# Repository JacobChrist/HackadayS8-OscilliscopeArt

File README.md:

# Oscilloscope Art at Hackaday Supercon8 (2024)

This project is documented here:

https://hackaday.io/project/198922-oscilloscope-art-at-hackaday-supercon-8

This repo contains supporting schematics, code and spreadsheets (or at least that's the plan)

## Some notes from markusthegeek​:

Be sure to use the Earle Philhower library for the Pi Pico with the Arduino IDE.  You must press the boot button when powering the board to program it the first time when using the Arduino IDE.

When you clone the repo use the "sip-header-code" branch if you want to use it with the S8 Hackaday Badge

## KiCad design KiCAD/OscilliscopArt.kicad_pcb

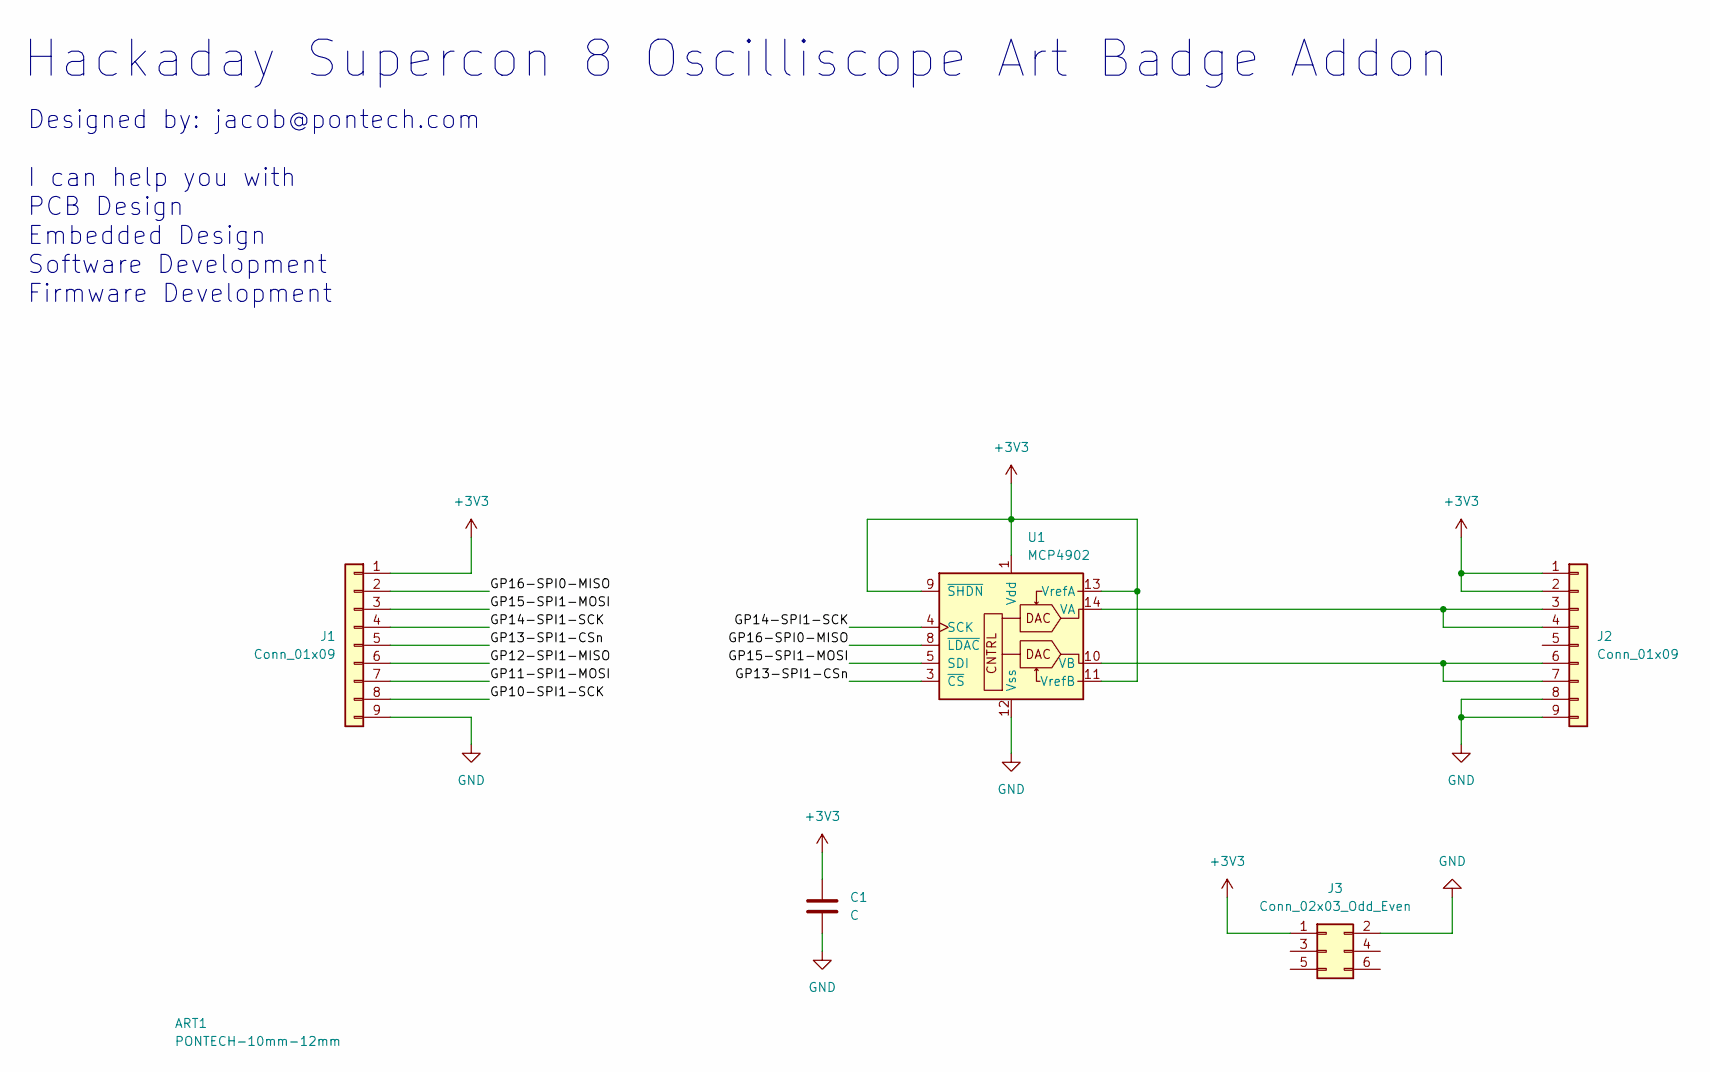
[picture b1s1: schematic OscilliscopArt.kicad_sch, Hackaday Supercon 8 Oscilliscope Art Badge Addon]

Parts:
ART1: PONTECH-10mm-12mm
C1: C; C_Disc_D5.0mm_W2.5mm_P2.50mm
J1, J2: Conn_01x09; SIP-9_22.3x3mm_P2.54mm
J3: Conn_02x03_Odd_Even; PinHeader_2x03_P2.54mm_Vertical
U1: MCP4902; DIP-14_W7.62mm_LongPads

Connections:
+3V3: C1.1, J1.1, J2.1, J2.2, J3.1, U1.1 (Vdd), U1.9 (~SHDN), U1.11 (VrefB), U1.13 (VrefA)
/GP10-SPI1-SCK: J1.8
/GP11-SPI1-MOSI: J1.7
/GP12-SPI1-MISO: J1.6
/GP13-SPI1-CSn: J1.5, U1.3 (~CS)
/GP14-SPI1-SCK: J1.4, U1.4 (SCK)
/GP15-SPI1-MOSI: J1.3, U1.5 (SDI)
/GP16-SPI0-MISO: J1.2, U1.8 (~LDAC)
GND: C1.2, J1.9, J2.8, J2.9, J3.2, U1.12 (Vss)
unnamed: J2.3, J2.4, U1.14 (VA)
unnamed: J2.6, J2.7, U1.10 (VB)

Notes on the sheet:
Hackaday Supercon 8 Oscilliscope Art Badge Addon
Designed by: jacob@pontech.com I can help you with PCB Design Embedded Design Software Development Firmware Development

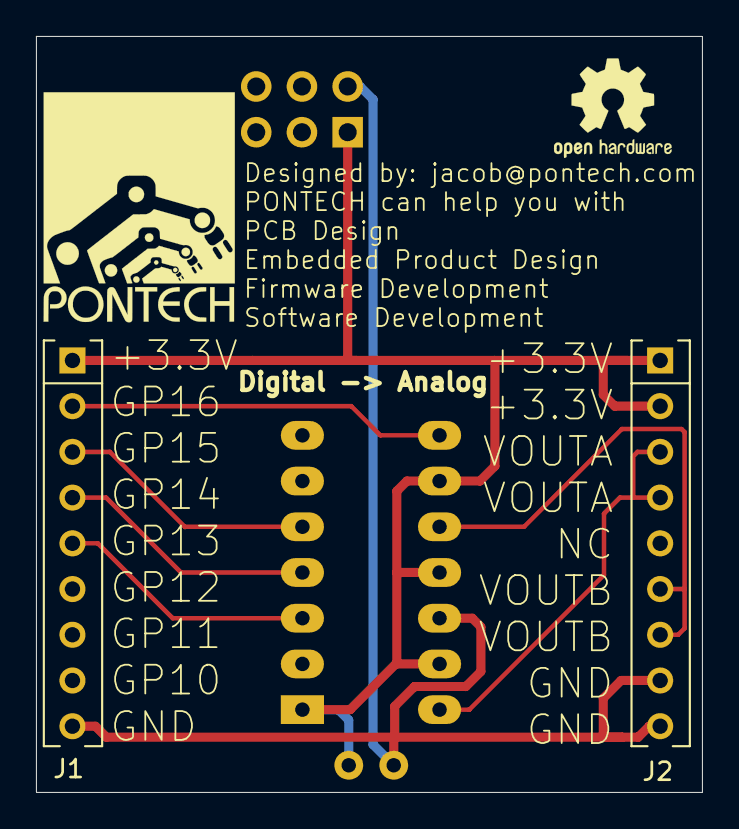
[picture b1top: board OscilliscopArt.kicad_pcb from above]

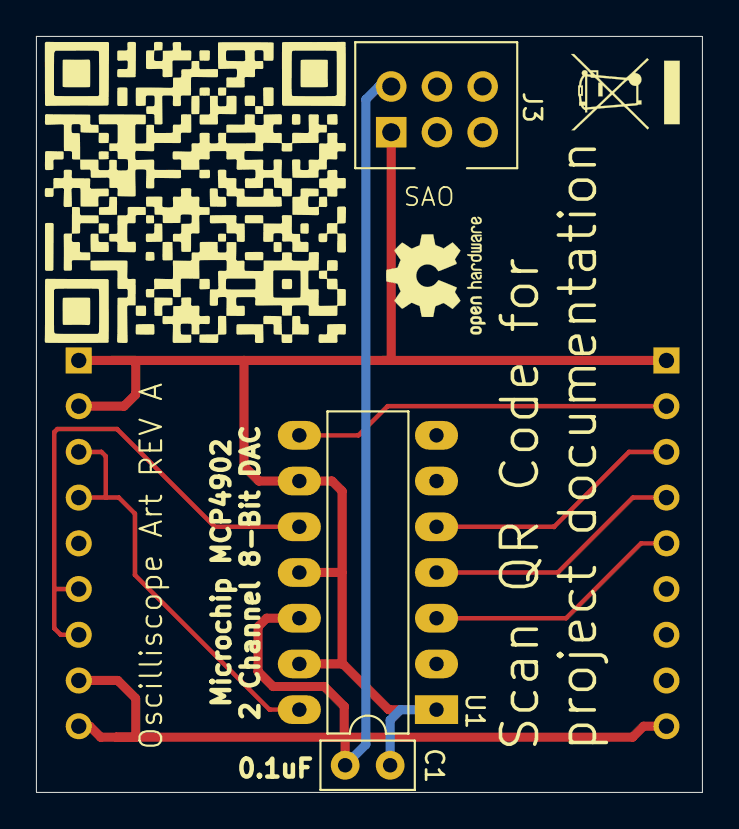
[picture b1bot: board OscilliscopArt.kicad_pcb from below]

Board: 2 copper layers, 37.0 x 42.0 mm, 6 parts (3 on the bottom side), 8 nets.

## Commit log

2024-10-20 Inital commit
2024-10-20 Added source code for the demo being shown at Supercon8
2024-10-21 Added SAO header
2024-10-21 REV-A Gerbers + Added WEE and Open Hardware Logos
2024-10-21 Added Excel Spreadsheet for generating art as code.
2024-11-01 Updated SPI port and chip select pins for running the boards off the SIP header on the back of the badge.
2025-06-24 Converted project to KiCad 9.x
